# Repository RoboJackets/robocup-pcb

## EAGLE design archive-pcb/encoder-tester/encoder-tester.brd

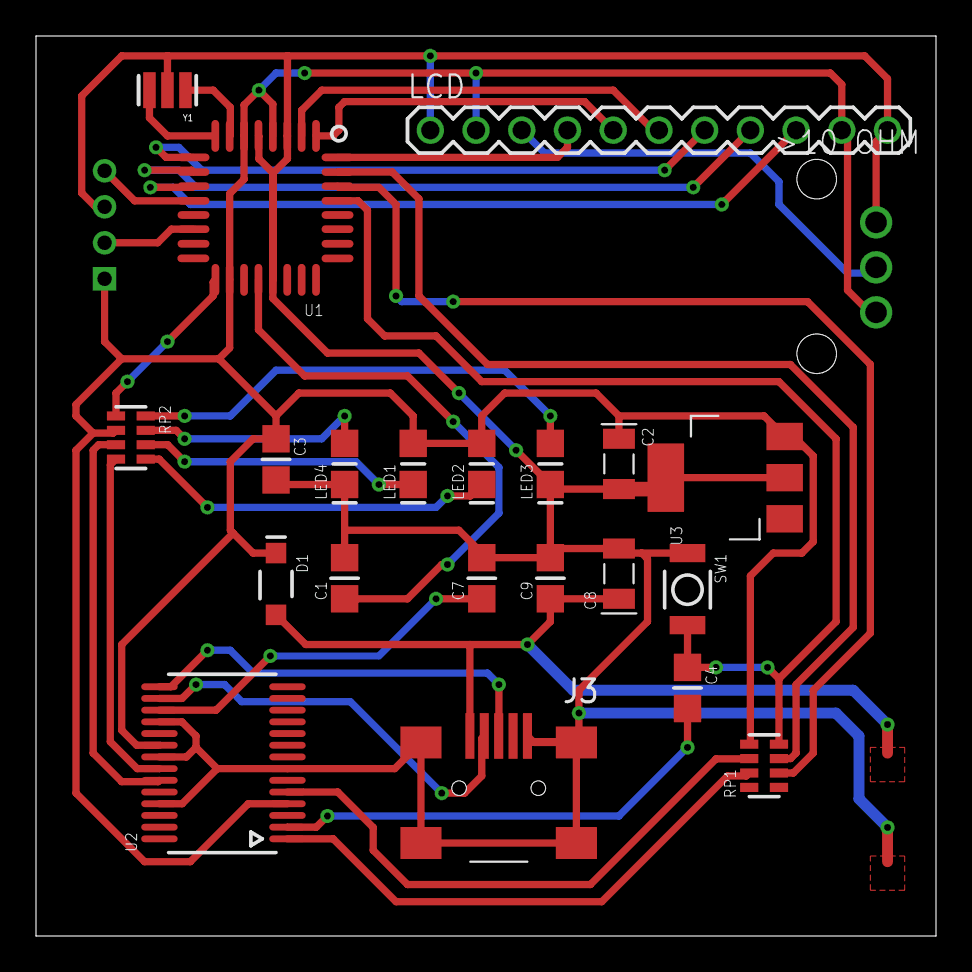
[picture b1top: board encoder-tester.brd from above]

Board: 2 copper layers, 50.0 x 50.0 mm, 23 parts (1 on the bottom side), 31 nets.

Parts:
C1, C3, C4, C7, C9: 0.1uF; CAP0805-NP
C2, C8: 4.7uF; TAN-A
D1: MBR0520; SOD-123
J3: USB-MINI-B%C; USB-MINI-B_2
J6: 2MM-4V; 2MM-4-V
LCD: M11PTH; 1X11
LED1: RED_RX; LED0805
LED2: GREEN_TX; LED0805
LED3: L_AMBER; LED0805
LED4: BLUE; LED0805
RP1: 1K; RES4NT
RP2: 330; RES4NT
SW1: RESET; 157SW
U1: ATMEGA168-20AU; QFP032
U2: FT232RL; SSOP28
U3: UA78M05; SOT223
U$7: 10OHMPOT; POTFOOT
Y1: 16MHz; RESONATOR

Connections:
3V3: C7.1, U2.17
+5V: C2.1, C3.1, D1.1, J6.1, LCD.2, LCD.10, LED1.2, LED2.2, RP1.5, RP2.2, U1.4, U1.6, U1.18, U2.4, U2.20, U3.3, U$7.1
AREF: C1.1, U1.20
COM: C1.2, C2.2, C3.2, C7.2, C8.2, C9.2, J3.1, J3.6, J3.7, J3.8, J3.9, J6.3, LCD.1, LCD.11, LED3.1, LED4.1, SW1.1, U1.3, U1.5, U1.21, U2.7, U2.18, U2.21, U2.25, U3.2, U3.4, U$7.3, Y1.2
D0/RX: RP1.2, U1.30
D1/TX: RP1.3, U1.31
D2: LCD.4, U1.32
D3: LCD.5, U1.1
D4: LCD.6, U1.2
D5: LCD.7, U1.9
D6: LCD.8, U1.10
D7: LCD.9, U1.11
D8: J6.4, U1.12
D10: J6.2, U1.14
D13/SCK: RP2.1, U1.17
unnamed: U1.8, Y1.3
unnamed: U1.7, Y1.1
unnamed: LED4.2, RP2.7
unnamed: C4.2, U2.2
unnamed: J3.3, U2.15
unnamed: J3.4, U2.16
unnamed: LED3.2, RP2.8
unnamed: RP2.3, U2.23
unnamed: RP2.4, U2.22
unnamed: LED1.1, RP2.6
unnamed: LED2.1, RP2.5
POT: LCD.3, U$7.2
RESET: C4.1, RP1.4, SW1.2, U1.29
RX: RP1.7, U2.1
TX: RP1.6, U2.5
VUSB: C8.1, C9.1, D1.2, J3.5

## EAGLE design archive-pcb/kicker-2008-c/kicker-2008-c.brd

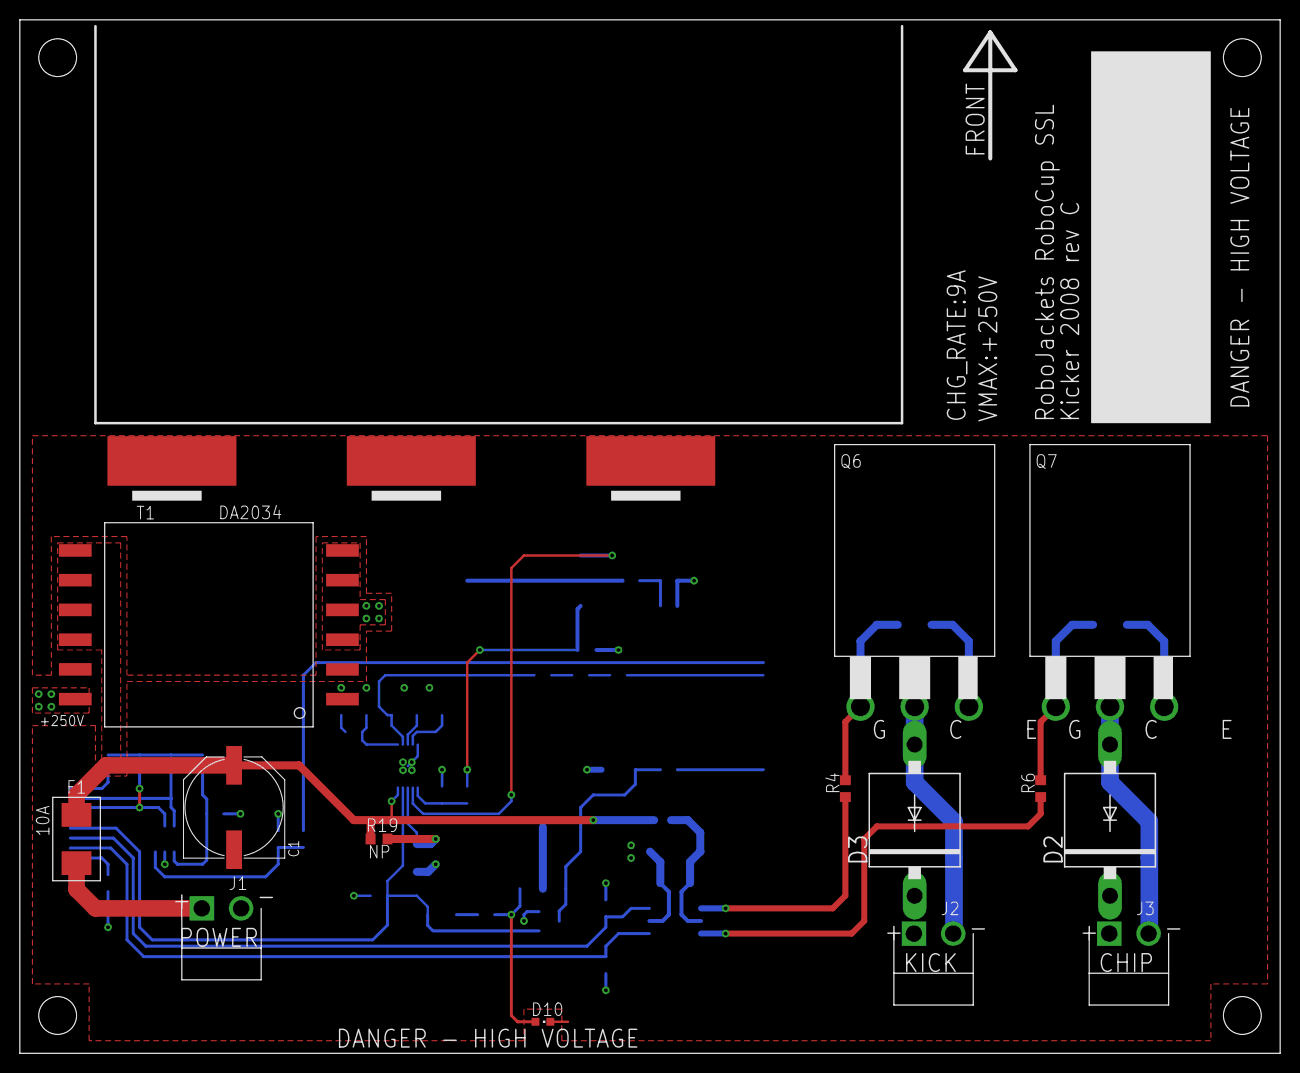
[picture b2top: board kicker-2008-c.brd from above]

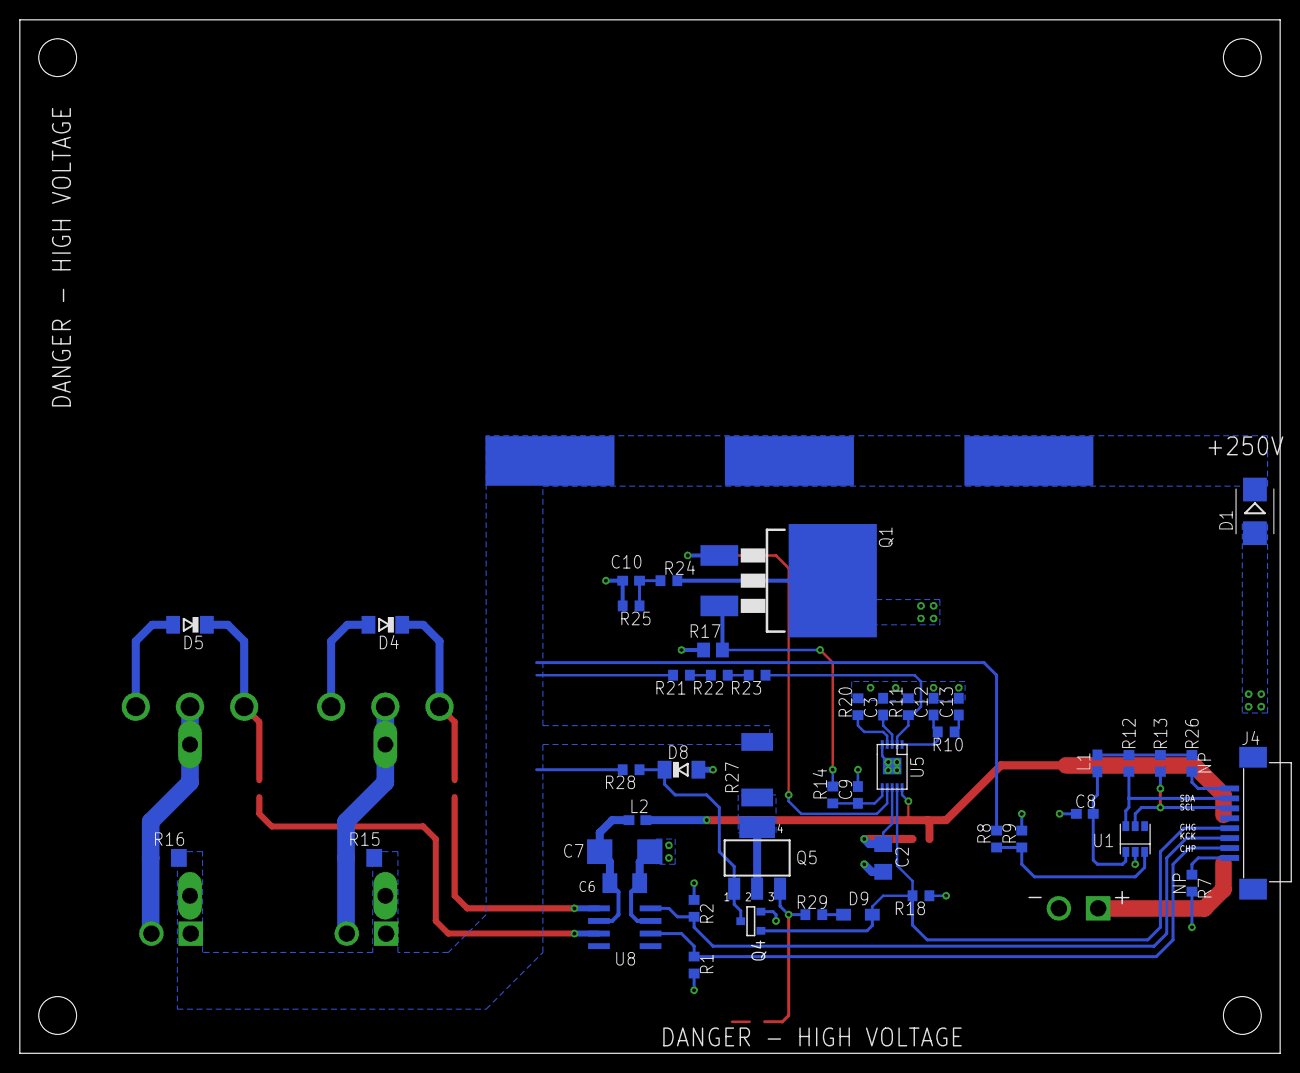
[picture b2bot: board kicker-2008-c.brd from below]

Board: 2 copper layers, 127.0 x 104.1 mm, 64 parts (47 on the bottom side), 39 nets.

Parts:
C1: UWT1E471MNL1GS; PANASONIC_G
C2: 4.7uF, 25v; C1206
C3, C8: 100nF; C0603
C6: 4.7uF; C1206K
C7: 47uF; C/6032-28R
C9, C13: 22nF; C0603
C10: 220pF 100V; C0603
C12: 100pF; C0603
D1: STTH3R06U; SMB
D2, D3: 6A6-T; P6-15
D4, D5, D8: BZV55-B18,115; SOD80C
D9: BAS16H; SOD323-W
D10: LTST-S270KRKT; CHIPLED_0603
F1: 10A; NANO2_157
J1: POWER; JST_VH_2_RA
J2: KICK_R; JST_VH_2_RA
J3: KICK_L; JST_VH_2_RA
J4: 0528520870
L1, L2: HZ0603B102R-10; C0603
Q1: STB40NF20; D2PACK
Q4: FDV303N; SOT-23
Q5: FQT1N80; SOT223
Q6, Q7: IXGX400N30A3; PLUS247
R1, R2, R9, R12, R13, R18: 10.0k; R0603
R4, R6: 10; R0603
R7, R19, R25, R26: NP; R0603
R8: 1.00M; R0603
R10: 6.8k; R0603
R11: 16.20k, 1% (MCR03EZPFX1622); R0603
R14, R24: 22; R0603
R15, R16: 680K; R1206
R17: 0.015 (ERJ-6BWFR015V); R0805
R20: 140k; R0603
R21: 470k 1%; R0603
R22, R23: 1.00M, 1% (MCR03EZPFX1004); R0603
R27: RHC2512FT33K0; R2512
R28: 10M; R0603
R29: 220; R0603
T1: DA2034
U1: ADC081C027; SOT23-6
U5: LT3757; MSOP-10-MSE
U8: TC4427; SO08
U$3, U$4, U$5: EET-UQ2E821CA; 22CAP

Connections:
+3V3: L1.1, R12.2, R13.2, R26.2
+12V: C1.+, F1.P$2, L2.2, R19.1, T1.7, T1.8, T1.9, T1.10, U5.10
CHARGE: D9.A, J4.4, Q4.3, R18.2, U5.9
CHIP: J4.2, R1.2, U8.2
GND: C1.-, C2.2, C3.2, C6.2, C7.-, C8.2, C9.2, C10.2, C12.2, C13.2, D4.A, D5.A, D8.A, D10.C, J1.2, Q4.2, Q6.P$3, Q7.P$3, R1.1, R2.1, R7.2, R9.1, R11.1, R17.1, R18.1, R20.2, R25.1, T1.1, U1.2, U5.5, U5.11, U8.3, U$3.2, U$4.2, U$5.2
HV: D1.C, D2.C, D3.C, J2.1, J3.1, R8.2, R15.2, R16.2, R21.2, R27.2, R28.2, U$3.1, U$4.1, U$5.1
KICK: J4.3, R2.2, U8.4
unnamed: D5.C, Q7.P$1, R6.2
unnamed: Q1.1, U5.7
unnamed: J4.1, R7.1
unnamed: C12.1, R10.1, U5.1
unnamed: C13.1, R10.2
unnamed: R22.1, R23.2
unnamed: D4.C, Q6.P$1, R4.2
unnamed: R8.1, R9.2, U1.3
unnamed: D2.A, J3.2, Q7.P$2, R16.1
unnamed: J4.8, R26.1
unnamed: R4.1, U8.5
unnamed: R6.1, U8.7
unnamed: D3.A, J2.2, Q6.P$2, R15.1
unnamed: C6.1, C7.+, L2.1, U8.6
unnamed: C8.1, L1.2, U1.1
unnamed: D8.C, Q4.1, Q5.1, R28.1
unnamed: Q5.2, Q5.4, R27.1
unnamed: R21.1, R22.2
unnamed: R11.2, R23.1, U5.2
unnamed: F1.P$1, J1.1
unnamed: Q1.2, R24.2, T1.3, T1.4, T1.5, T1.6
unnamed: C3.1, U5.3
unnamed: R20.1, U5.4
unnamed: C2.1, R19.2, U5.8
unnamed: D10.A, Q5.3, R29.2
unnamed: C9.1, R14.1, U5.6
unnamed: C10.1, R24.1, R25.2
unnamed: D9.C, R29.1
unnamed: D1.A, T1.12
NAG: Q1.3, R14.2, R17.2
SCL: J4.6, R13.1, U1.5
SDA: J4.7, R12.1, U1.6

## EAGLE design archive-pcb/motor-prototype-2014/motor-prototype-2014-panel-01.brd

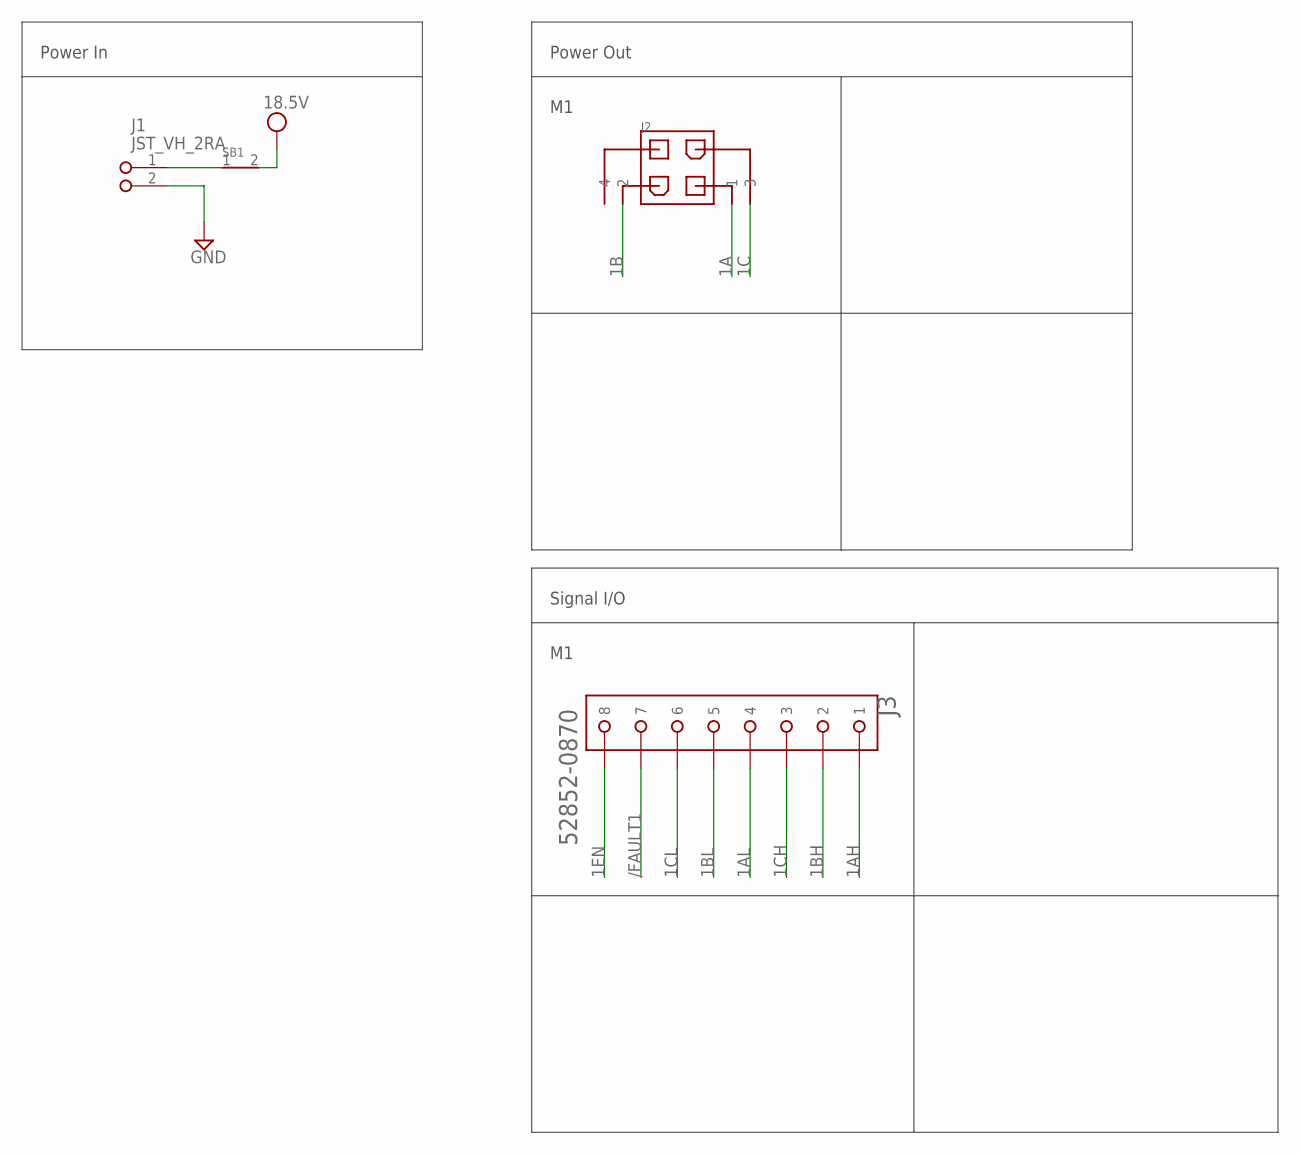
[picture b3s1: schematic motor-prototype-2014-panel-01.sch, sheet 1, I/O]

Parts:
J1: JST_VH_2RA; JST_VH_2_RA
J2: MINIFITJR_HDR_2X2; MINIFITJR_HDR_2X2_RA
J3: 52852-0870; 52852-08
SB1: SOLDERBRIDGESB1206; SB1206

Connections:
1A: J2.P$1 (1); also elsewhere on the board
1AH: J3.1; also elsewhere on the board
1AL: J3.4; also elsewhere on the board
1B: J2.P$2 (2); also elsewhere on the board
1BH: J3.2; also elsewhere on the board
1BL: J3.5; also elsewhere on the board
1C: J2.P$3 (3); also elsewhere on the board
1CH: J3.3; also elsewhere on the board
1CL: J3.6; also elsewhere on the board
1EN: J3.8; also elsewhere on the board
/FAULT1: J3.7; also elsewhere on the board
GND: J1.2; also elsewhere on the board
VCC: SB1.2; also elsewhere on the board
V_IN: J1.1, SB1.1

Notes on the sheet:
Power In
Power Out
Signal I/O

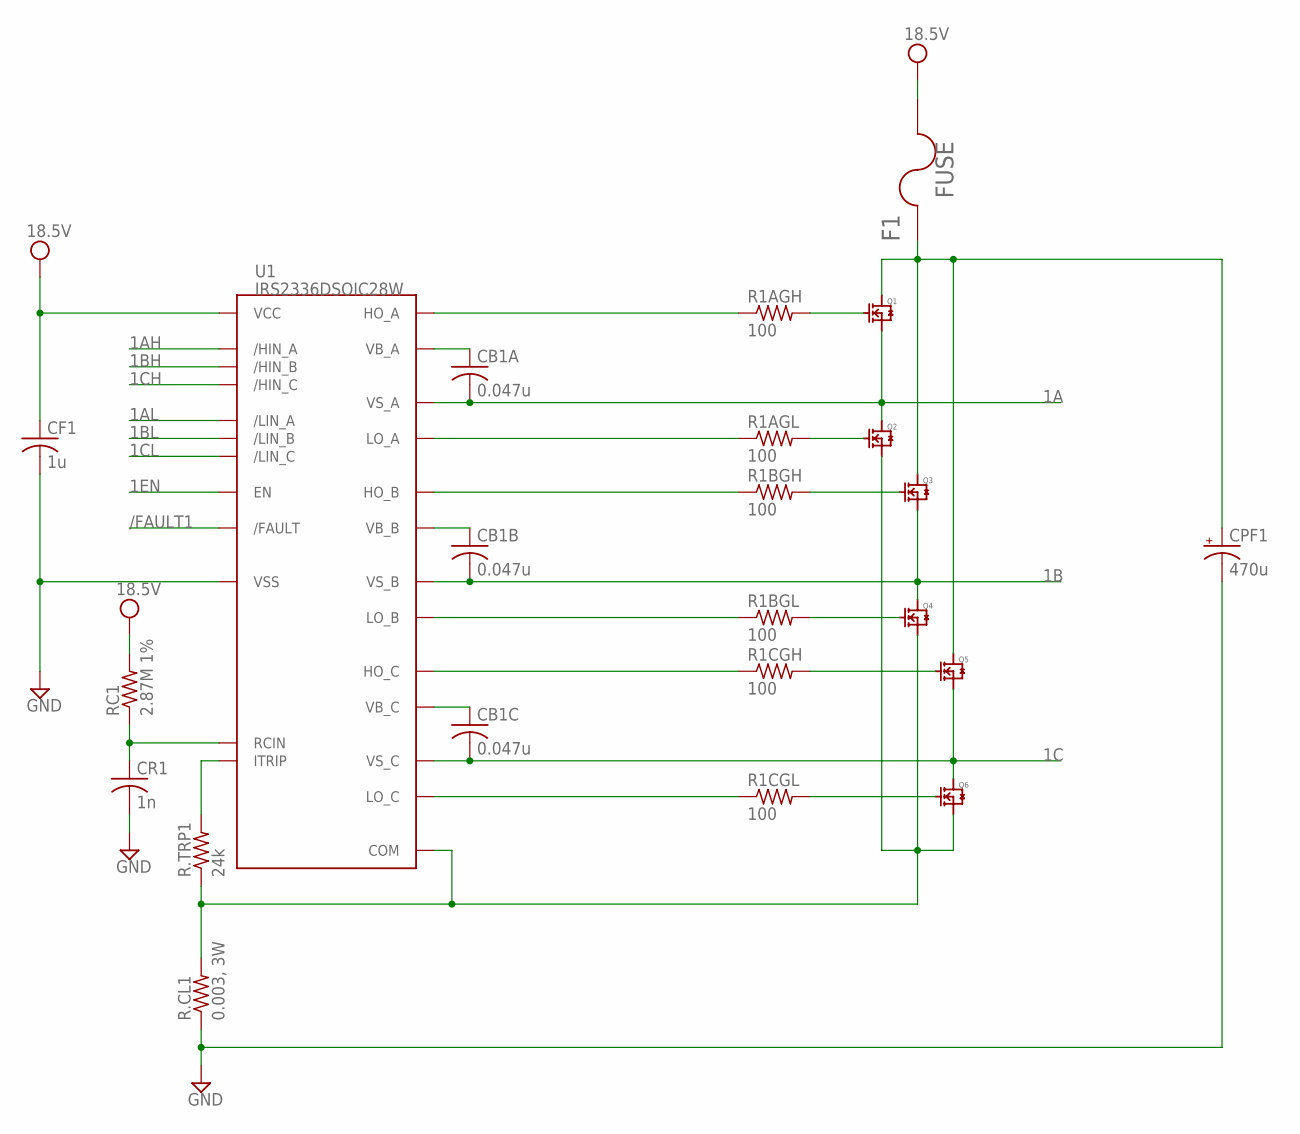
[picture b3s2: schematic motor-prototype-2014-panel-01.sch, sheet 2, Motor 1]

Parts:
CB1A, CB1B, CB1C: 0.047u; C1206
CF1: 1u; C0603
CPF1: 470u; PANASONIC_G
CR1: 1n; C0603
F1: FUSE; FUSE_MINI_ATC
Q1, Q2, Q3, Q4, Q5, Q6: SIR438DP; POWERPAK_SO8
R1AGH, R1AGL, R1BGH, R1BGL, R1CGH, R1CGL: 100; R0603
R.CL1: 0.003, 3W; R2512
R.TRP1: 24k; R0603
RC1: 2.87M 1%; R0603
U1: IRS2336DSOIC28W; SO-28W

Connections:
1A: CB1A.2, Q1.1 (S), Q1.2 (S), Q1.3 (S), Q2.5 (D), U1.26 (VS_A); also elsewhere on the board
1AH: U1.2 (/HIN_A); also elsewhere on the board
1AL: U1.5 (/LIN_A); also elsewhere on the board
1B: CB1B.2, Q3.1 (S), Q3.2 (S), Q3.3 (S), Q4.5 (D), U1.22 (VS_B); also elsewhere on the board
1BH: U1.3 (/HIN_B); also elsewhere on the board
1BL: U1.6 (/LIN_B); also elsewhere on the board
1C: CB1C.2, Q5.1 (S), Q5.2 (S), Q5.3 (S), Q6.5 (D), U1.18 (VS_C); also elsewhere on the board
1CH: U1.4 (/HIN_C); also elsewhere on the board
1CL: U1.7 (/LIN_C); also elsewhere on the board
1EN: U1.10 (EN); also elsewhere on the board
/FAULT1: U1.8 (/FAULT); also elsewhere on the board
GND: CF1.2, CPF1.-, CR1.2, R.CL1.1, U1.12 (VSS); also elsewhere on the board
unnamed: R1AGH.1, U1.27 (HO_A)
unnamed: Q1.4 (G), R1AGH.2
unnamed: Q2.4 (G), R1AGL.2
unnamed: R1AGL.1, U1.16 (LO_A)
unnamed: R1BGH.1, U1.23 (HO_B)
unnamed: R1BGL.1, U1.15 (LO_B)
unnamed: R1CGL.1, U1.14 (LO_C)
unnamed: R1CGH.1, U1.19 (HO_C)
unnamed: Q3.4 (G), R1BGH.2
unnamed: Q5.4 (G), R1CGH.2
unnamed: Q6.4 (G), R1CGL.2
unnamed: Q4.4 (G), R1BGL.2
unnamed: CR1.1, RC1.1, U1.11 (RCIN)
unnamed: R.TRP1.2, U1.9 (ITRIP)
PGND_1: Q2.1 (S), Q2.2 (S), Q2.3 (S), Q4.1 (S), Q4.2 (S), Q4.3 (S), Q6.1 (S), Q6.2 (S), Q6.3 (S), R.CL1.2, R.TRP1.1, U1.13 (COM)
VB_1A: CB1A.1, U1.28 (VB_A)
VB_1B: CB1B.1, U1.24 (VB_B)
VB_1C: CB1C.1, U1.20 (VB_C)
VCC: CF1.1, F1.2.1 (2), F1.2.2 (2), RC1.2, U1.1 (VCC); also elsewhere on the board
VM1: CPF1.+, F1.1.1 (1), F1.1.2 (1), Q1.5 (D), Q3.5 (D), Q5.5 (D)

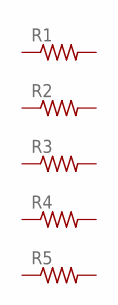
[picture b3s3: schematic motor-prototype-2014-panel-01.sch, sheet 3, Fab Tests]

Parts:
R1: R-US_R0201; R0201
R2: R-US_R0402; R0402
R3: R-US_R0603; R0603
R4: R-US_R0805; R0805
R5: R-US_R1206; R1206

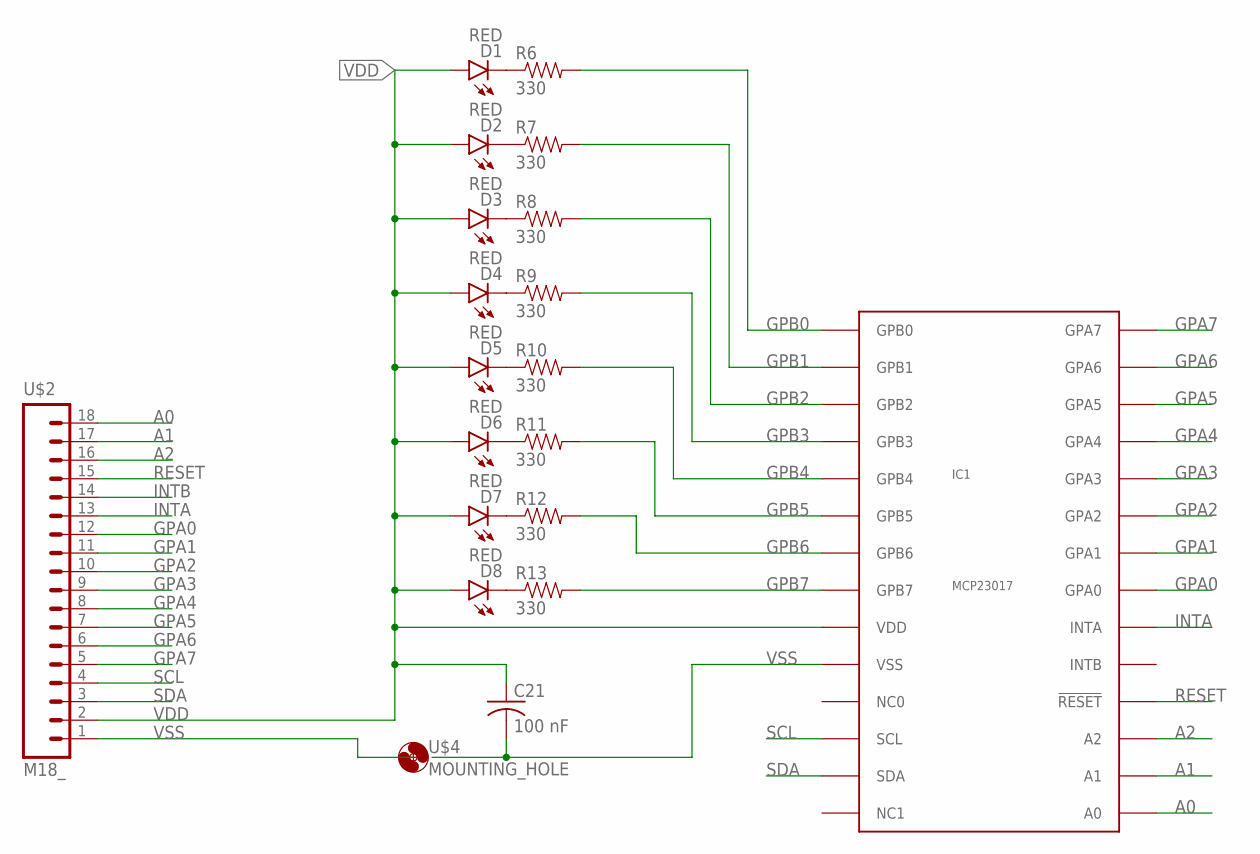
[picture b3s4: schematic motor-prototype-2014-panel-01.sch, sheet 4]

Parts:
C21: 100 nF; C0603
D1, D2, D3, D4, D5, D6, D7, D8: RED; LED-0603
IC1: MCP23017; SSOP-28
R6, R7, R8, R9, R10, R11, R12, R13: 330; 0603-RES
U$2: M18_; 1X18
U$4: MOUNTING_HOLE

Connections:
A0: IC1.15 (A0), U$2.18; also elsewhere on the board
A1: IC1.16 (A1), U$2.17
A2: IC1.17 (A2), U$2.16
GPA0: IC1.21 (GPA0), U$2.12
GPA1: IC1.22 (GPA1), U$2.11
GPA2: IC1.23 (GPA2), U$2.10
GPA3: IC1.24 (GPA3), U$2.9
GPA4: IC1.25 (GPA4), U$2.8
GPA5: IC1.26 (GPA5), U$2.7
GPA6: IC1.27 (GPA6), U$2.6
GPA7: IC1.28 (GPA7), U$2.5
GPB0: IC1.1 (GPB0), R6.2
GPB1: IC1.2 (GPB1), R7.2
GPB2: IC1.3 (GPB2), R8.2
GPB3: IC1.4 (GPB3), R9.2
GPB4: IC1.5 (GPB4), R10.2
GPB5: IC1.6 (GPB5), R11.2
GPB6: IC1.7 (GPB6), R12.2
GPB7: IC1.8 (GPB7), R13.2
INTA: IC1.20 (INTA), U$2.13
INTB: U$2.14
unnamed: D1.C, R6.1
unnamed: D2.C, R7.1
unnamed: D3.C, R8.1
unnamed: D4.C, R9.1
unnamed: D5.C, R10.1
unnamed: D6.C, R11.1
unnamed: D7.C, R12.1
unnamed: D8.C, R13.1
RESET: IC1.18 (!RESET!), U$2.15; also elsewhere on the board
SCL: IC1.12 (SCL), U$2.4
SDA: IC1.13 (SDA), U$2.3
VDD: C21.1, D1.A, D2.A, D3.A, D4.A, D5.A, D6.A, D7.A, D8.A, IC1.9 (VDD), U$2.2; also elsewhere on the board
VSS: C21.2, IC1.10 (VSS), U$2.1, U$4.GND; also elsewhere on the board

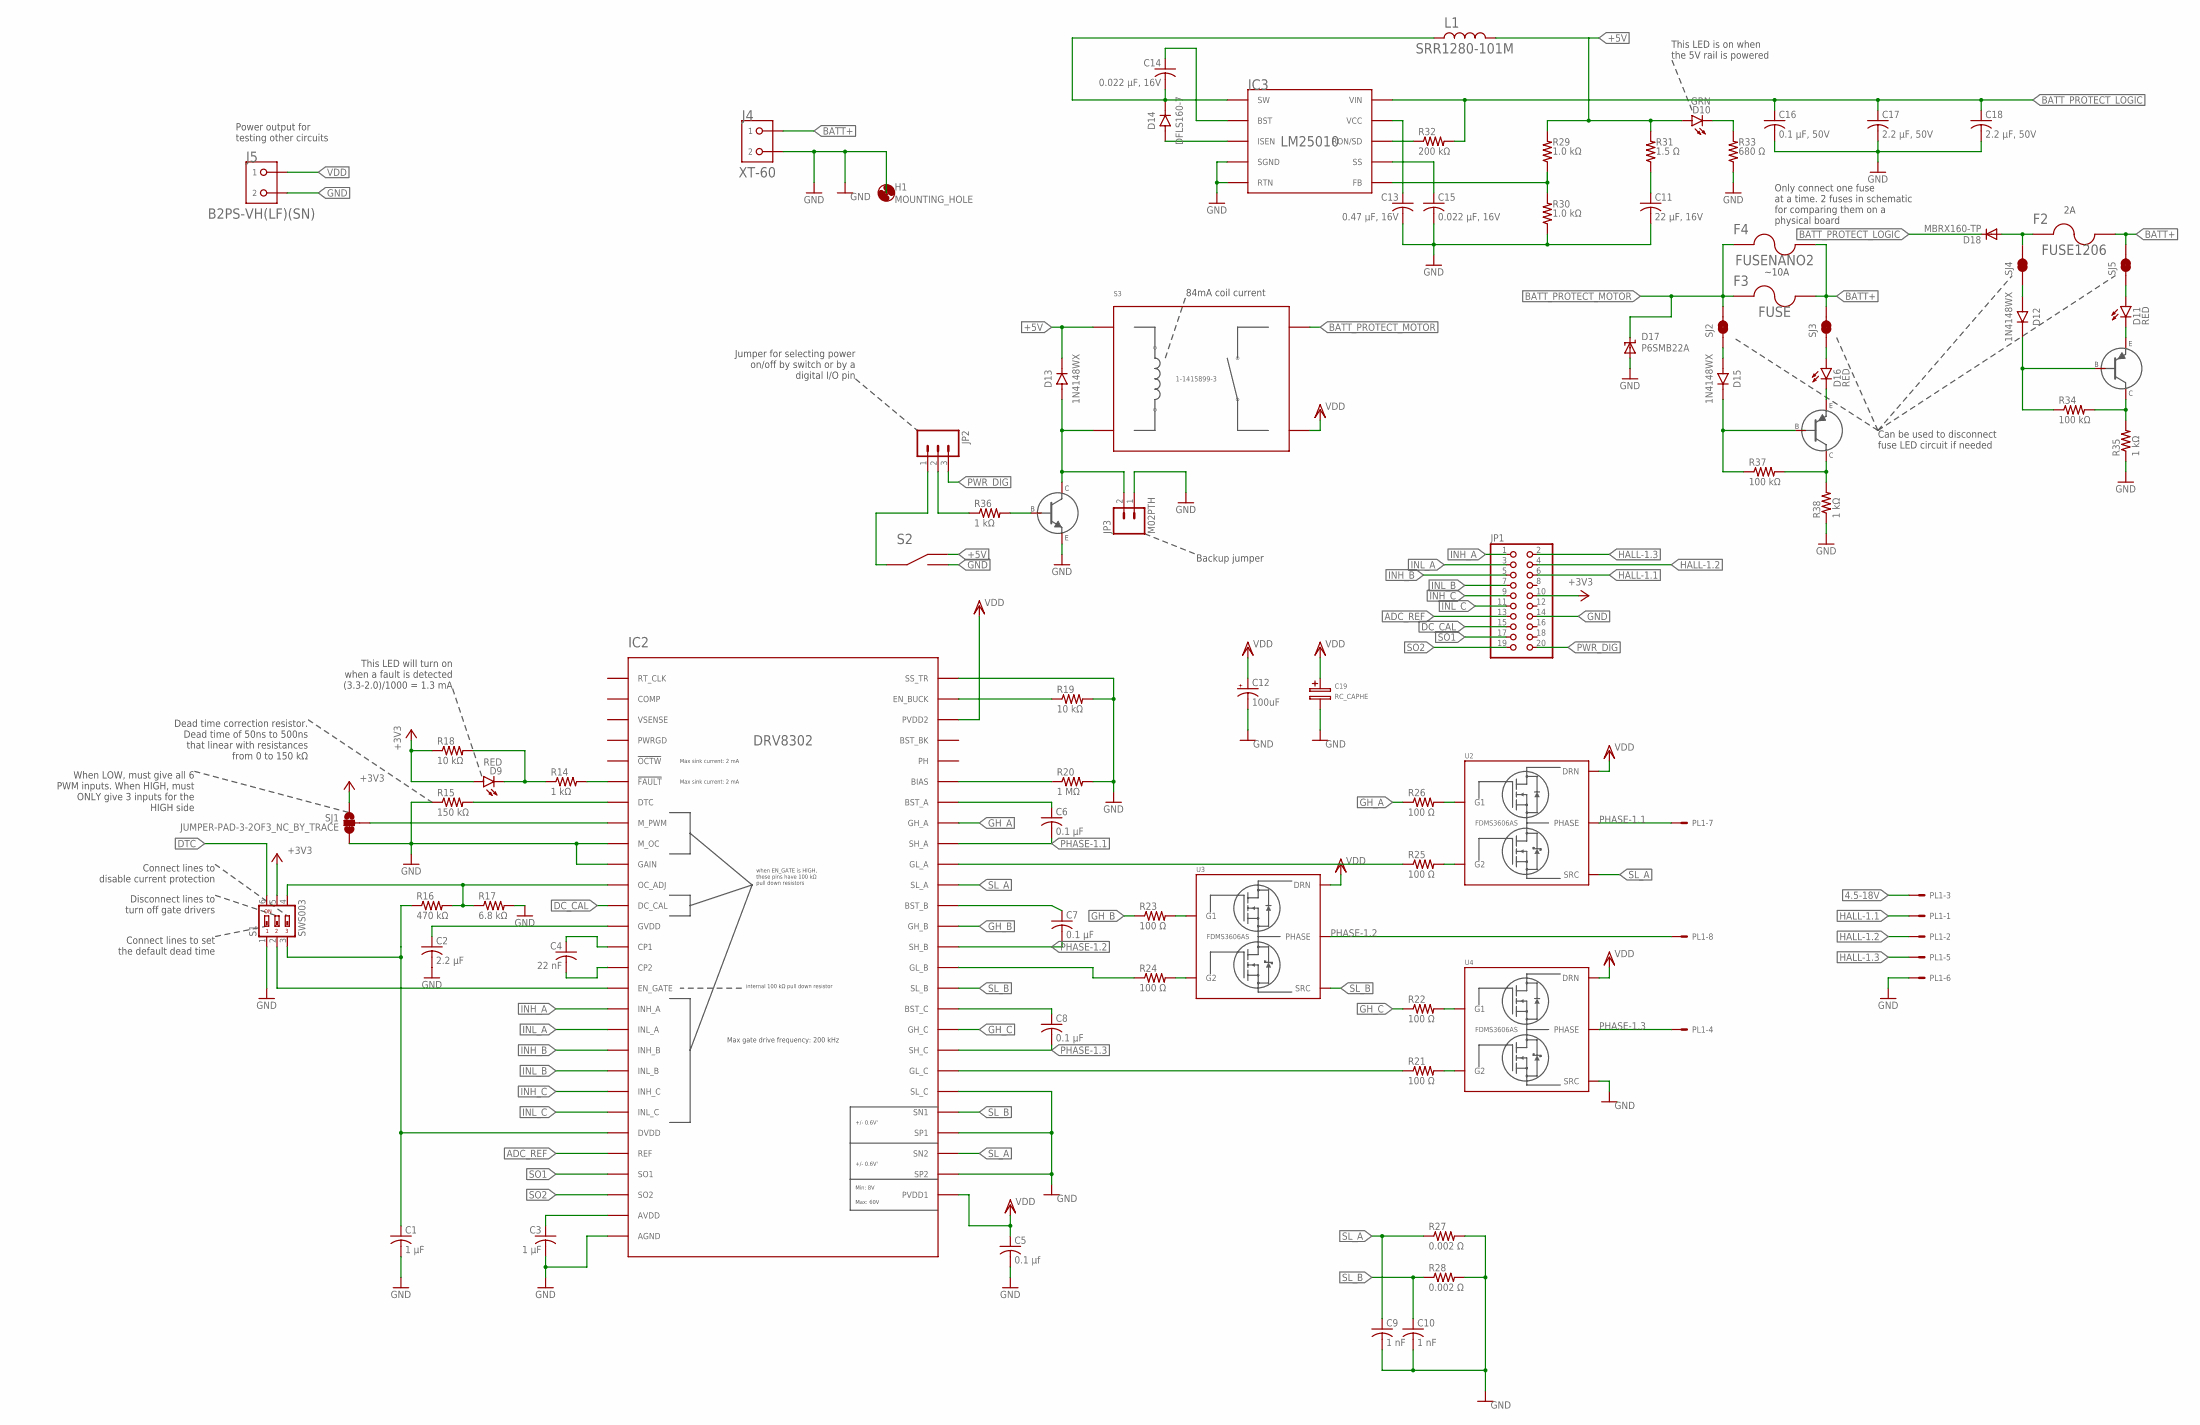
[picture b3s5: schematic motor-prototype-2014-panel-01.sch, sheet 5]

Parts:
C1, C3: 1 µF; C0603
C2: 2.2 µF; C0603
C4: 22 nF; C1206
C5: 0.1 µf; C0603
C6, C7, C8: 0.1 µF; C0402
C9, C10: 1 nF; C0402
C11: 22 µF, 16V; C0402
C12: 100uF; PANASONIC_H13
C13: 0.47 µF, 16V; C0402
C14, C15: 0.022 µF, 16V; C0402
C16: 0.1 µF, 50V; C0603
C17, C18: 2.2 µF, 50V; C0603
C19: RC_CAPHE; HE_SERIES
D9, D11, D16: RED; LED-0603
D10: GRN; LED-0603
D12, D13, D15: 1N4148WX; SOD-323
D14: DFLS160-7; POWERDI-123
D17: P6SMB22A; SMBJ
D18: MBRX160-TP; SOD123
F2: FUSE1206; F1206
F3: FUSE; FUSE_MINI_ATC
F4: FUSENANO2; NANO2_157
H1: MOUNTING_HOLE
IC2: DRV8302; TSSOP-56_3
IC3: LM25010; 10-WDFN
J4: XT-60
J5: B2PS-VH(LF)(SN); B2PS
JP1: PINHD-2X10; 2X10
JP2: M03PTH; 1X03
JP3: M02PTH; 1X02
L1: SRR1280-101M; SRR1280
PL1: 555X-8V; 5566-8
Q7, Q9: BJT-PNP_; SOT-23-3
Q8: MMBT2222A-TP; SOT-23-3
R14, R35, R36, R38: 1 kΩ; R0402
R15: 150 kΩ; R0603
R16: 470 kΩ; R0402
R17: 6.8 kΩ; R0402
R18, R19: 10 kΩ; R0402
R20: 1 MΩ; R0402
R21, R22, R23, R24, R25, R26: 100 Ω; R0402
R27, R28: 0.002 Ω; R1206
R29, R30: 1.0 kΩ; R0402
R31: 1.5 Ω; R0402
R32: 200 kΩ; R0402
R33: 680 Ω; R0402
R34, R37: 100 kΩ; R0402
S1: SWS003; SMS-003
S2: 34EWMSP12MRT; 34EWMSP12M6RT
S3: 1-1415899-3
SJ1: JUMPER-PAD-3-2OF3_NC_BY_TRACE; PAD-JUMPER-3-2OF3_NC_BY_TRACE_YES_SILK_FULL_BOX
SJ2, SJ3, SJ4, SJ5: JUMPER-PAD-2-NC_BY_TRACE; PAD-JUMPER-2-NC_BY_TRACE_YES_SILK
U2, U3, U4: FDMS3606AS; PQFN-(DUAL)

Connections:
4.5-18V: PL1.3
!FAULT!: IC2.6 (!FAULT!), R14.2
+3V3: D9.A, JP1.10, R18.1, S1.5, SJ1.1
+5V: D10.A, D13.C, L1.P$1, R29.2, R31.2, S2.1 (OFF), S3.A1 (2)
ADC_REF: IC2.24 (REF), JP1.13
BATT+: F2.2, F3.2.1 (2), F3.2.2 (2), F4.P$2 (2), J4.BATT (1), SJ3.2, SJ5.2
BATT_PROTECT_LOGIC: C16.1, C17.1, C18.1, D18.C, IC3.P10.1 (VIN), IC3.P10.2 (VIN), R32.2
BATT_PROTECT_MOTOR: D17.C, F3.1.1 (1), F3.1.2 (1), F4.P$1 (1), S3.14.1 (3), S3.14.2 (3), SJ2.2
BIAS: IC2.49 (BIAS), R20.1
BOB: D18.A, F2.1, SJ4.2
BST_A: C6.1, IC2.48 (BST_A)
BST_B: C7.1, IC2.43 (BST_B)
BST_BK: IC2.52 (BST_BK)
BST_C: C8.1, IC2.38 (BST_C)
CP1: C4.1, IC2.14 (CP1)
CP2: C4.2, IC2.15 (CP2)
DC_CAL: IC2.12 (DC_CAL), JP1.15
DTC: IC2.7 (DTC), R15.2, S1.6
GH_A: IC2.47 (GH_A), R26.1
GH_A_F: R26.2, U2.1 (G1)
GH_B: IC2.42 (GH_B), R23.1
GH_B_F: R23.2, U3.1 (G1)
GH_C: IC2.37 (GH_C), R22.1
GH_C_F: R22.2, U4.1 (G1)
GL_A: IC2.45 (GL_A), R25.1
GL_A_F: R25.2, U2.8 (G2)
GL_B: IC2.40 (GL_B), R24.1
GL_B_F: R24.2, U3.8 (G2)
GL_C: R21.2, U4.8 (G2)
GND: C1.2, C2.2, C3.2, C5.2, C9.2, C10.2, C11.2, C12.-, C13.2, C15.2, C16.2, C17.2, C18.2, C19.NEG (-), D17.A, H1.GND, IC2.9 (M_OC), IC2.10 (GAIN), IC2.28 (AGND), IC2.30 (SP2), IC2.32 (SP1), IC2.34 (SL_C), IC2.56 (SS_TR), IC2.57 (AGND), IC2.58 (AGND), IC2.59 (AGND), IC3.P4.1 (SGND), IC3.P4.2 (SGND), IC3.P5.1 (RTN), IC3.P5.2 (RTN), IC3.P_CENTER (SGND), J4.GND (2), J5.2, JP1.14, JP3.1, PL1.6, Q8.S (E), R15.1, R17.2, R19.2, R20.2, R27.2, R28.2, R30.1, R33.1, R35.1, R38.1, S1.1, S2.3 (ON), SJ1.3, U4.5 (SRC), U4.6 (SRC), U4.7 (SRC); also elsewhere on the board
HALL-1.1: JP1.6, PL1.1
HALL-1.2: JP1.4, PL1.2
HALL-1.3: JP1.2, PL1.5
INH_A: IC2.17 (INH_A), JP1.1
INH_B: IC2.19 (INH_B), JP1.5
INH_C: IC2.21 (INH_C), JP1.9
INL_A: IC2.18 (INL_A), JP1.3
INL_B: IC2.20 (INL_B), JP1.7
INL_C: IC2.22 (INL_C), JP1.11
M_PWM: IC2.8 (M_PWM), SJ1.2
unnamed: D9.C, R14.1, R18.2
unnamed: IC2.11 (OC_ADJ), R16.2, R17.1, S1.4
unnamed: C2.1, IC2.13 (GVDD)
unnamed: C3.1, IC2.27 (AVDD)
unnamed: C1.1, IC2.23 (DVDD), R16.1, S1.3
unnamed: IC2.55 (EN_BUCK), R19.1
unnamed: IC2.35 (GL_C), R21.1
unnamed: C15.1, IC3.P7.1 (SS), IC3.P7.2 (SS)
unnamed: C13.1, IC3.P9.1 (VCC), IC3.P9.2 (VCC)
unnamed: IC3.P6.1 (FB), IC3.P6.2 (FB), R29.1, R30.2
unnamed: IC3.P8.1 (RON/SD), IC3.P8.2 (RON/SD), R32.1
unnamed: C11.1, R31.1
unnamed: C14.1, IC3.P2.1 (BST), IC3.P2.2 (BST)
unnamed: C14.2, D14.C, IC3.P1.1 (SW), IC3.P1.2 (SW), L1.P$2
unnamed: D10.C, R33.2
unnamed: D12.C, Q7.G (B), R34.1
unnamed: D11.C, Q7.S (E)
unnamed: Q7.D (C), R34.2, R35.2
unnamed: D14.A, IC3.P3.1 (ISEN), IC3.P3.2 (ISEN)
unnamed: IC2.16 (EN_GATE), S1.2
unnamed: D13.A, JP3.2, Q8.D (C), S3.A2 (6)
unnamed: Q8.G (B), R36.2
unnamed: D16.C, Q9.S (E)
unnamed: D15.C, Q9.G (B), R37.1
unnamed: Q9.D (C), R37.2, R38.2
unnamed: JP2.2, R36.1
unnamed: JP2.1, S2.2 (C)
unnamed: D15.A, SJ2.1
unnamed: D16.A, SJ3.1
unnamed: D12.A, SJ4.1
unnamed: D11.A, SJ5.1
PHASE-1.1: C6.2, IC2.46 (SH_A), PL1.7, U2.CENTER (PHASE)
PHASE-1.2: C7.2, IC2.41 (SH_B), PL1.8, U3.CENTER (PHASE)
PHASE-1.3: C8.2, IC2.36 (SH_C), PL1.4, U4.CENTER (PHASE)
PWR_DIG: JP1.20, JP2.3
SL_A: C9.1, IC2.31 (SN2), IC2.44 (SL_A), R27.1, U2.5 (SRC), U2.6 (SRC), U2.7 (SRC)
SL_B: C10.1, IC2.33 (SN1), IC2.39 (SL_B), R28.1, U3.5 (SRC), U3.6 (SRC), U3.7 (SRC)
SO1: IC2.25 (SO1), JP1.17
SO2: IC2.26 (SO2), JP1.19
VDD: C5.1, C12.+, C19.POS (+), IC2.29 (PVDD1), IC2.53 (PVDD2), IC2.54 (PVDD2), J5.1, S3.11.1 (5), S3.11.2 (5), U2.2 (DRN), U2.3 (DRN), U2.4 (DRN), U2.LARGE_1 (DRN), U2.LARGE_2 (DRN), U2.LARGE_3 (DRN), U3.2 (DRN), U3.3 (DRN), U3.4 (DRN), U3.LARGE_1 (DRN), U3.LARGE_2 (DRN), U3.LARGE_3 (DRN), U4.2 (DRN), U4.3 (DRN), U4.4 (DRN), U4.LARGE_1 (DRN), U4.LARGE_2 (DRN), U4.LARGE_3 (DRN); also elsewhere on the board

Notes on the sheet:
Connect lines to disable current protection
Dead time correction resistor. Dead time of 50ns to 500ns that linear with resistances from 0 to 150 kΩ
Disconnect lines to turn off gate drivers
Connect lines to set the default dead time
This LED is on when the 5V rail is powered
This LED will turn on when a fault is detected (3.3-2.0)/1000 = 1.3 mA
When LOW, must give all 6 PWM inputs. When HIGH, must ONLY give 3 inputs for the HIGH side
84mA coil current
Backup jumper
Jumper for selecting power on/off by switch or by a digital I/O pin
Can be used to disconnect fuse LED circuit if needed
~10A
Only connect one fuse at a time. 2 fuses in schematic for comparing them on a physical board
Power output for testing other circuits

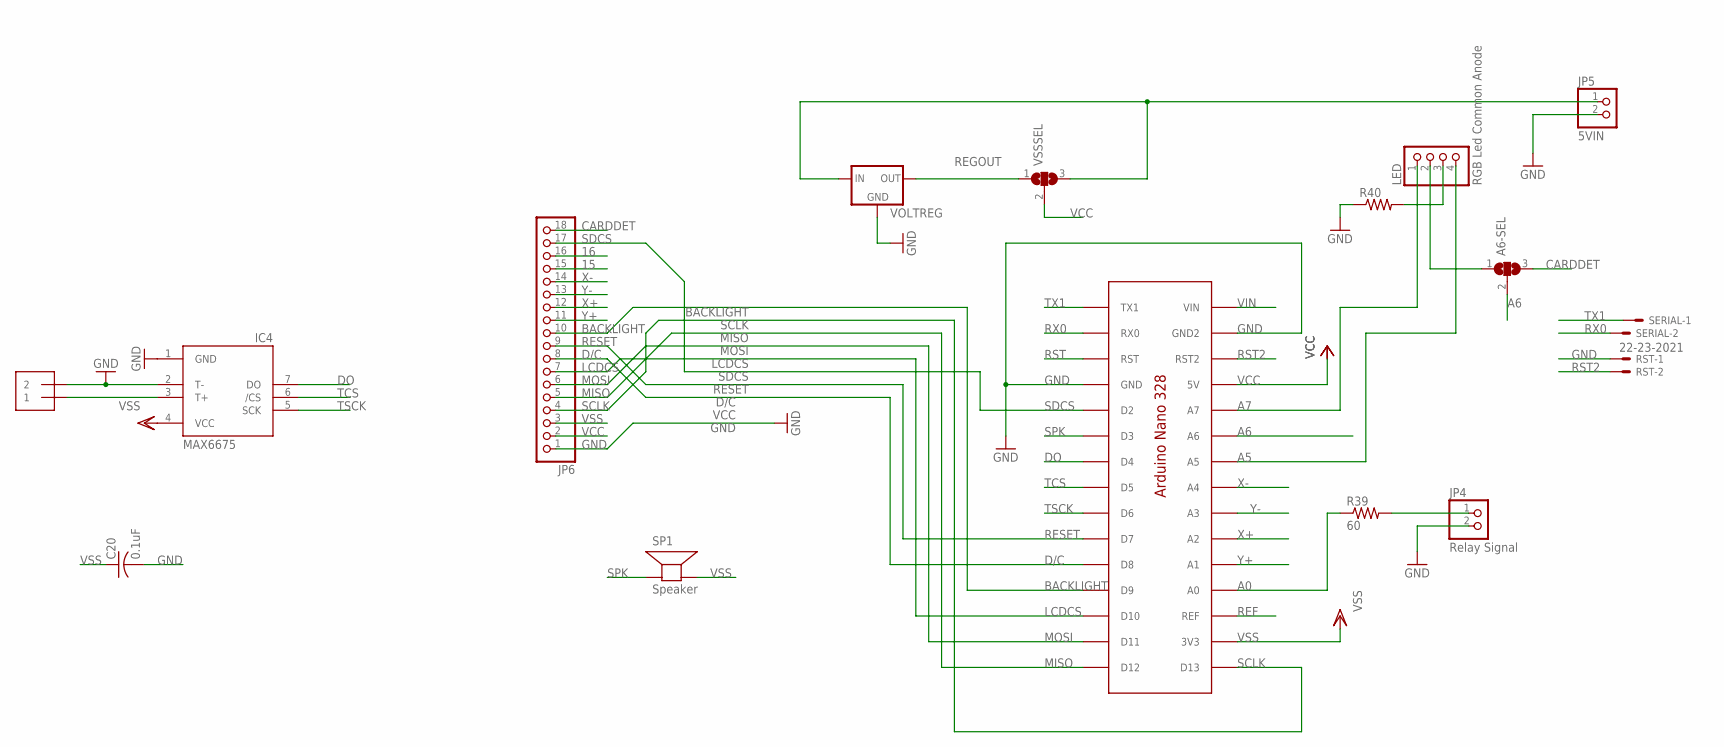
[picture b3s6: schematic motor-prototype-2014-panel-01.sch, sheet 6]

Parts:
A6-SEL: SJ2W; SJ_2
C20: 0.1uF; C0805K
IC4: MAX6675; SO08
JP4: Relay Signal; 1X02/90
JP5: 5VIN; 1X02/90
JP6: PINHD-1X18; 1X18
LED: RGB Led Common Anode; 1X04
R39: 60; M0805
R40: R-US_R0805; R0805
RST: 22-23-2021
SERIAL: 22-23-2021
SP1: Speaker; PS12
TCOUPLE: 1X2-3.5MM; 3.5MMTERM
U$7: ANANO3.3; ANANO3.0
VOLTREG: 78MXXS; 78SR
VSSSEL: SJ2W; SJ_2

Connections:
15: JP6.15
16: JP6.16
A0: R39.1, U$7.A0; also elsewhere on the board
A5: LED.4, U$7.A5
A6: A6-SEL.2, U$7.A6
A7: LED.1, U$7.A7
BACKLIGHT: JP6.10, U$7.D9
CARDDET: A6-SEL.3, JP6.18
D/C: JP6.8, U$7.D8
DO: IC4.7 (DO), U$7.D4
GND: C20.2, IC4.1 (GND), IC4.2 (T-), JP4.2, JP5.2, JP6.1, R40.1, RST.1, TCOUPLE.2, U$7.GND, U$7.GND2, VOLTREG.GND; also elsewhere on the board
LCDCS: JP6.7, U$7.D10
MISO: JP6.5, U$7.D12
MOSI: JP6.6, U$7.D11
unnamed: IC4.3 (T+), TCOUPLE.1
unnamed: JP4.1, R39.2
unnamed: LED.3, R40.2
unnamed: A6-SEL.1, LED.2
REF: U$7.REF
REGOUT: VOLTREG.OUT, VSSSEL.1
RESET: JP6.9, U$7.D7; also elsewhere on the board
RST: U$7.RST
RST2: RST.2, U$7.RST2
RX0: SERIAL.2, U$7.RX0
SCLK: JP6.4, U$7.D13
SDCS: JP6.17, U$7.D2
SPK: SP1.P$1 (+), U$7.D3
TCS: IC4.6 (/CS), U$7.D5
TRANSIN: JP5.1, VOLTREG.IN, VSSSEL.3
TSCK: IC4.5 (SCK), U$7.D6
TX1: SERIAL.1, U$7.TX1
VCC: JP6.2, U$7.5V, VSSSEL.2; also elsewhere on the board
VIN: U$7.VIN
VSS: C20.1, IC4.4 (VCC), JP6.3, SP1.P$2 (-), U$7.3V3; also elsewhere on the board
X+: JP6.12, U$7.A2
X-: JP6.14, U$7.A4
Y+: JP6.11, U$7.A1
Y-: JP6.13, U$7.A3

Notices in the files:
parts and their libraries:
SparkFun-Resistors: Licensing: Creative Commons ShareAlike 4.0 International - https://creativecommons.org/licenses/by-sa/4.0
